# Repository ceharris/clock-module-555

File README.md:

clock-module-555
================

This repository contains KiCad sources for a clock module based on a
design by Ben Eater as presented on his YouTube channel. Ben's version
of this module uses a mechanical toggle switch to select the free-running
or single-step mode. This version uses a more easily sourced push button
to toggle a flip-flop to select the mode. Both the mode select button
and the clock pulse button are debounced using 555 timers in monostable
configuration.

In free-running mode, the clock frequency can be varied using the 
on-board potentiometer, ranging from about 1 Hz to about 3 KHz.

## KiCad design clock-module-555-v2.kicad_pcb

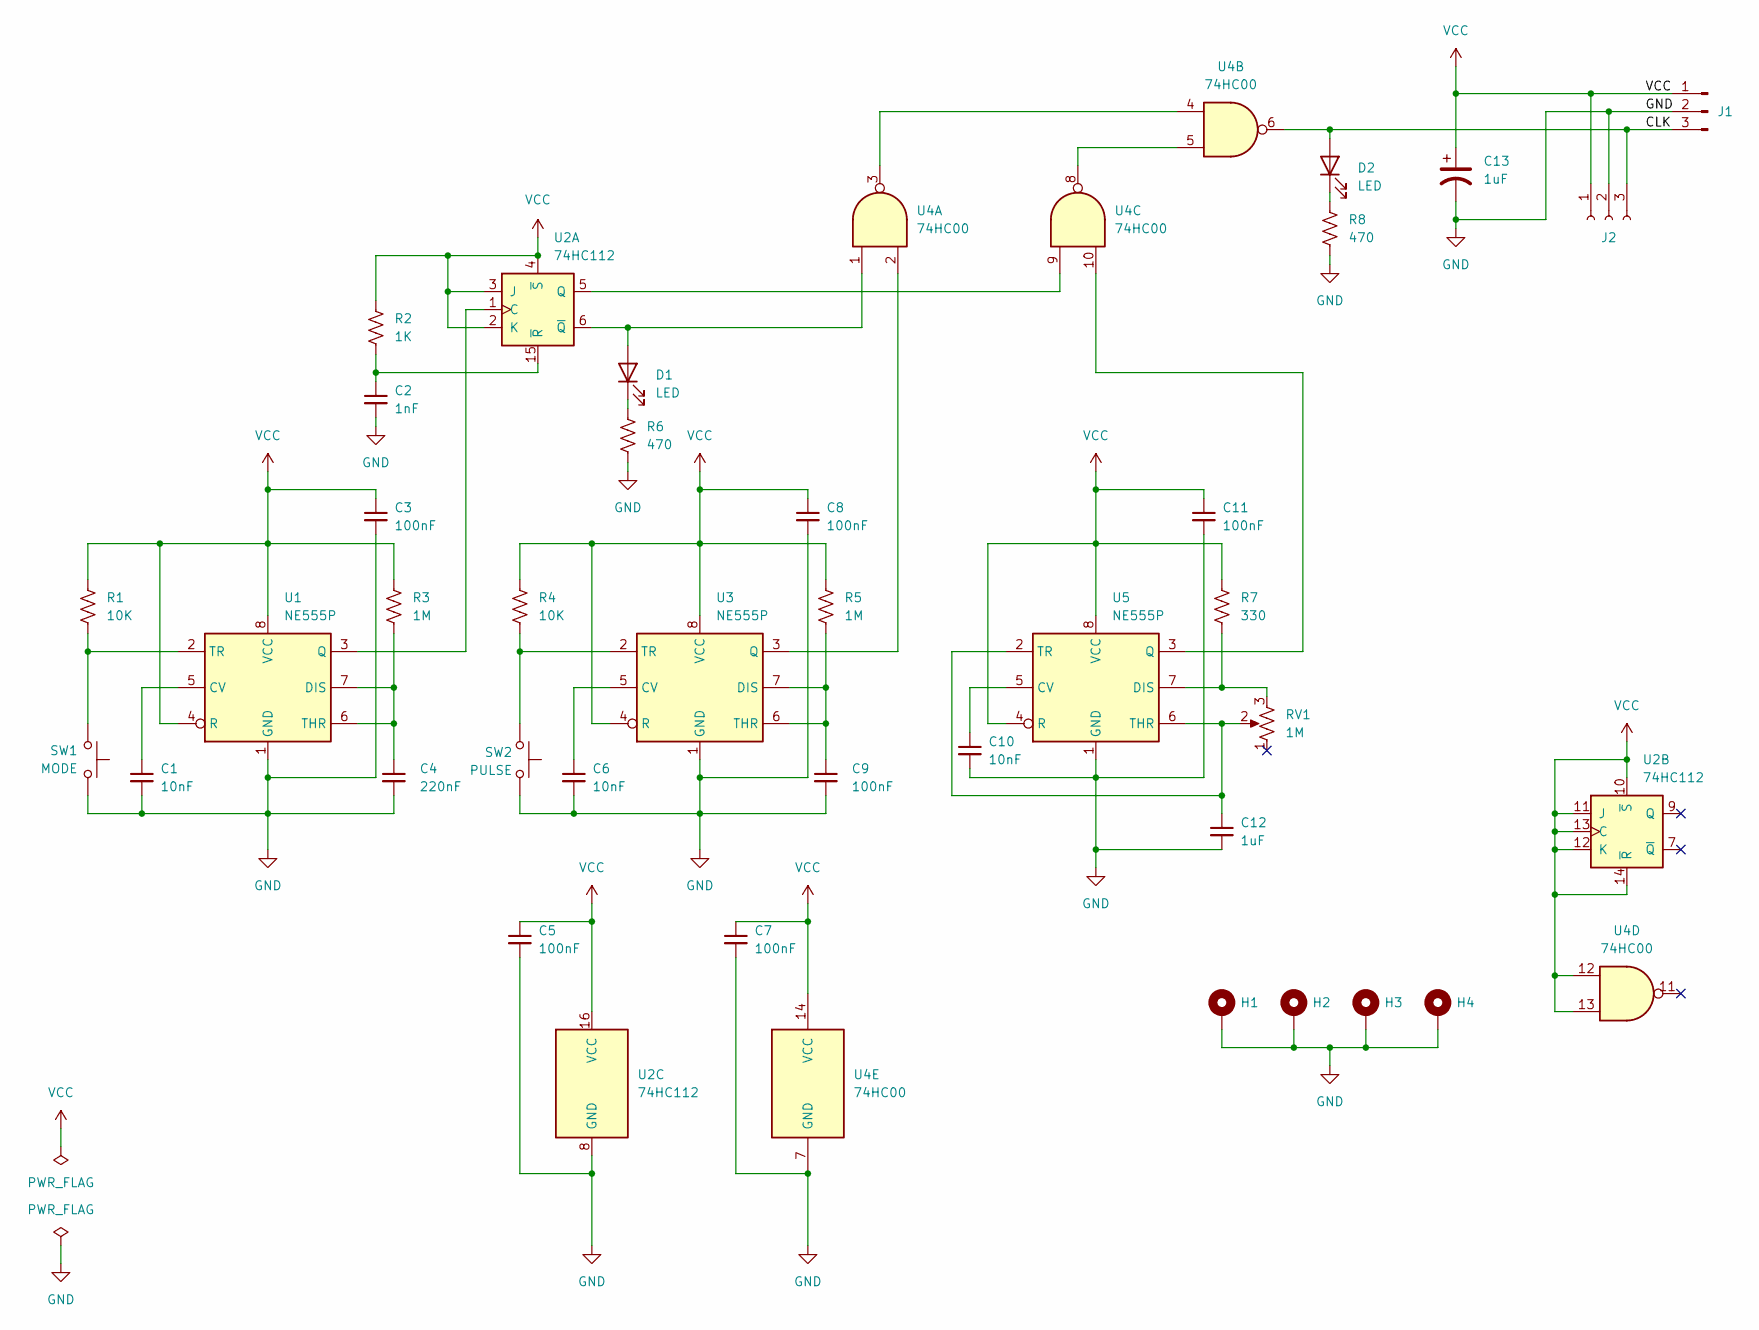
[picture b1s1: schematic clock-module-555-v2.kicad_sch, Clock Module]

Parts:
C1, C6, C10: 10nF; C_Disc_D3.0mm_W2.0mm_P2.50mm
C2: 1nF; C_Disc_D5.0mm_W2.5mm_P5.00mm
C3, C5, C7, C8, C11: 100nF; C_Disc_D3.0mm_W2.0mm_P2.50mm
C4: 220nF; C_Disc_D5.0mm_W2.5mm_P5.00mm
C9: 100nF; C_Disc_D5.0mm_W2.5mm_P5.00mm
C12: 1uF; C_Disc_D5.0mm_W2.5mm_P5.00mm
C13: 1uF; CP_Radial_D5.0mm_P2.00mm
D1, D2: LED; LED_D5.0mm
H1, H2, H3, H4: MountingHole_Pad; MountingHole_2.2mm_M2_DIN965_Pad
J1: Conn_01x03_Pin; PinHeader_1x03_P2.54mm_Horizontal
J2: Conn_01x03_Socket; PinSocket_1x03_P2.54mm_Vertical
R1, R4: 10K; R_Axial_DIN0207_L6.3mm_D2.5mm_P7.62mm_Horizontal
R2: 1K; R_Axial_DIN0207_L6.3mm_D2.5mm_P7.62mm_Horizontal
R3, R5: 1M; R_Axial_DIN0207_L6.3mm_D2.5mm_P7.62mm_Horizontal
R6, R8: 470; R_Axial_DIN0207_L6.3mm_D2.5mm_P7.62mm_Horizontal
R7: 330; R_Axial_DIN0207_L6.3mm_D2.5mm_P7.62mm_Horizontal
RV1: 1M; Potentiometer_Bourns_3386P_Vertical
SW1: MODE; SW_PUSH_6mm
SW2: PULSE; SW_PUSH-12mm
U1, U3, U5: NE555P; DIP-8_W7.62mm_Socket
U2: 74HC112; DIP-16_W7.62mm_Socket
U4: 74HC00; DIP-14_W7.62mm_Socket

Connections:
/CLK: D2.2 (A), J1.3, J2.3, U4.6
GND: C1.2, C2.2, C3.2, C4.2, C5.2, C6.2, C7.2, C8.2, C9.2, C10.2, C11.2, C12.2, C13.2, H1.1, H2.1, H3.1, H4.1, J1.2, J2.2, R6.2, R8.2, SW1.2, SW2.2, U1.1 (GND), U2.8 (GND), U3.1 (GND), U4.7 (GND), U5.1 (GND)
unnamed: D1.2 (A), U2.6 (~Q), U4.1
unnamed: D1.1 (K), R6.1
unnamed: D2.1 (K), R8.1
unnamed: C1.1, U1.5 (CV)
unnamed: C4.1, R3.2, U1.6 (THR), U1.7 (DIS)
unnamed: U1.3 (Q), U2.1 (C)
unnamed: R1.2, SW1.1, U1.2 (TR)
unnamed: U2.5 (Q), U4.9
unnamed: C2.1, R2.2, U2.15 (~R)
unnamed: C6.1, U3.5 (CV)
unnamed: C9.1, R5.2, U3.6 (THR), U3.7 (DIS)
unnamed: U3.3 (Q), U4.2
unnamed: R4.2, SW2.1, U3.2 (TR)
unnamed: U4.3, U4.4
unnamed: U4.5, U4.8
unnamed: C10.1, U5.5 (CV)
unnamed: R7.2, RV1.3, U5.7 (DIS)
unnamed: U4.10, U5.3 (Q)
unnamed: C12.1, RV1.2, U5.2 (TR), U5.6 (THR)
VCC: C3.1, C5.1, C7.1, C8.1, C11.1, C13.1, J1.1, J2.1, R1.1, R2.1, R3.1, R4.1, R5.1, R7.1, U1.4 (R), U1.8 (VCC), U2.2 (K), U2.3 (J), U2.4 (~S), U2.10 (~S), U2.11 (J), U2.12 (K), U2.13 (C), U2.14 (~R), U2.16 (VCC), U3.4 (R), U3.8 (VCC), U4.12, U4.13, U4.14 (VCC), U5.4 (R), U5.8 (VCC)

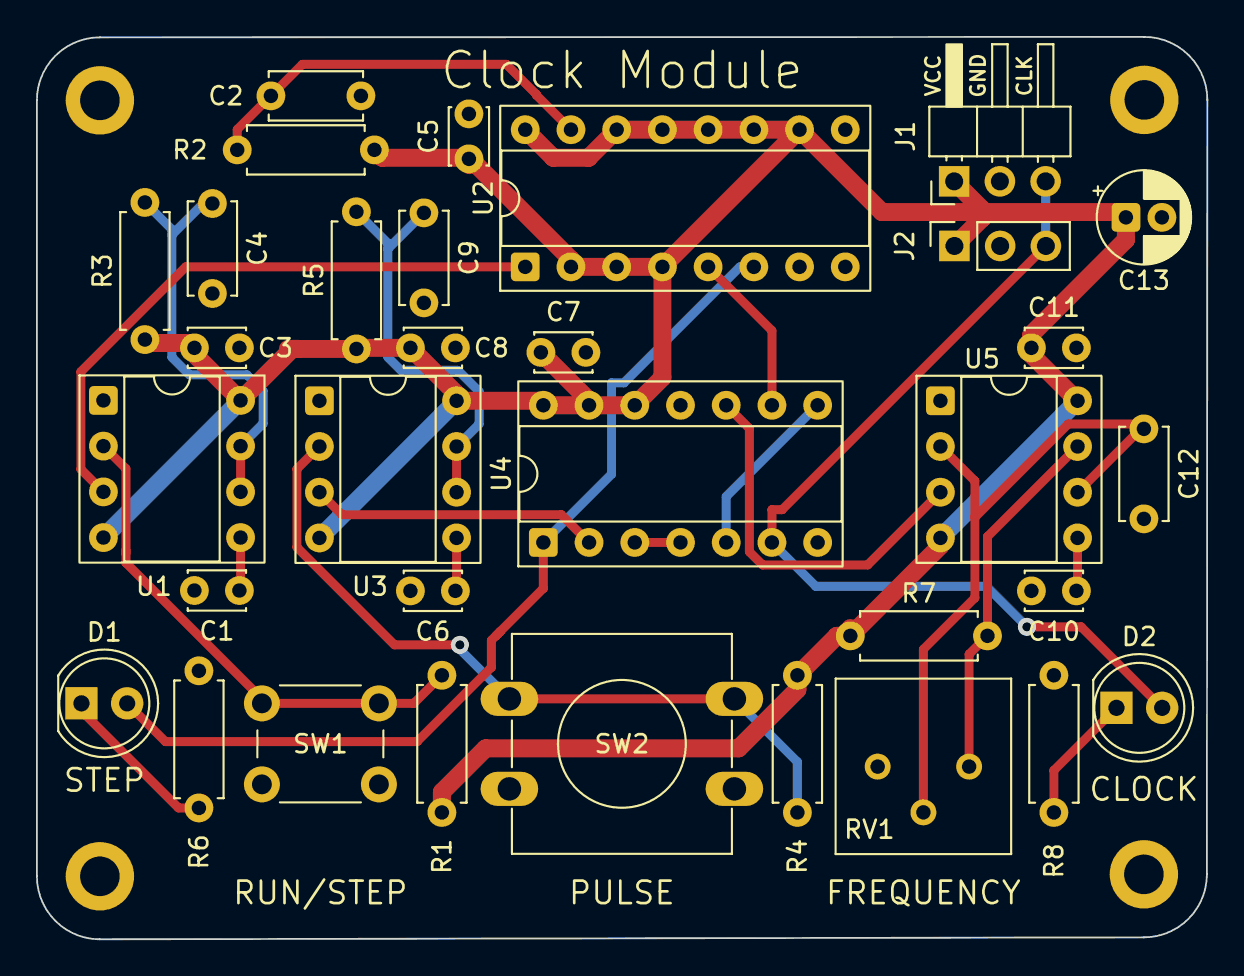
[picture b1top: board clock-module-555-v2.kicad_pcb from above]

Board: 2 copper layers, 65.0 x 50.1 mm, 37 parts (0 on the bottom side), 22 nets.

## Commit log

2025-07-08 revisions after first build
2025-07-08 added photo
2025-07-08 marked as rev 2
2025-07-08 added rev2 gerbers
2025-07-08 gerber setup
2025-07-08 set up to add PDF output in a release branch
2025-07-08 added PNGs for board to README
2025-07-08 revised PCB back image
2025-07-08 reduce whitespace
